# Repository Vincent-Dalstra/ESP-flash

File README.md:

# ESP-flash
A USB to UART Serial interface implementing a CH340C.

Designed primarily to program board with embedded ESP32 modules. USB-micro and USB-c for minimum I-have-the-wrong-cable

For compatibility with other programmers, it follow the the ESPFlash 1x6 Header convention. https://github.com/SuperHouse/ESPFlash
Big thanks to them for developing it and putting it out there.

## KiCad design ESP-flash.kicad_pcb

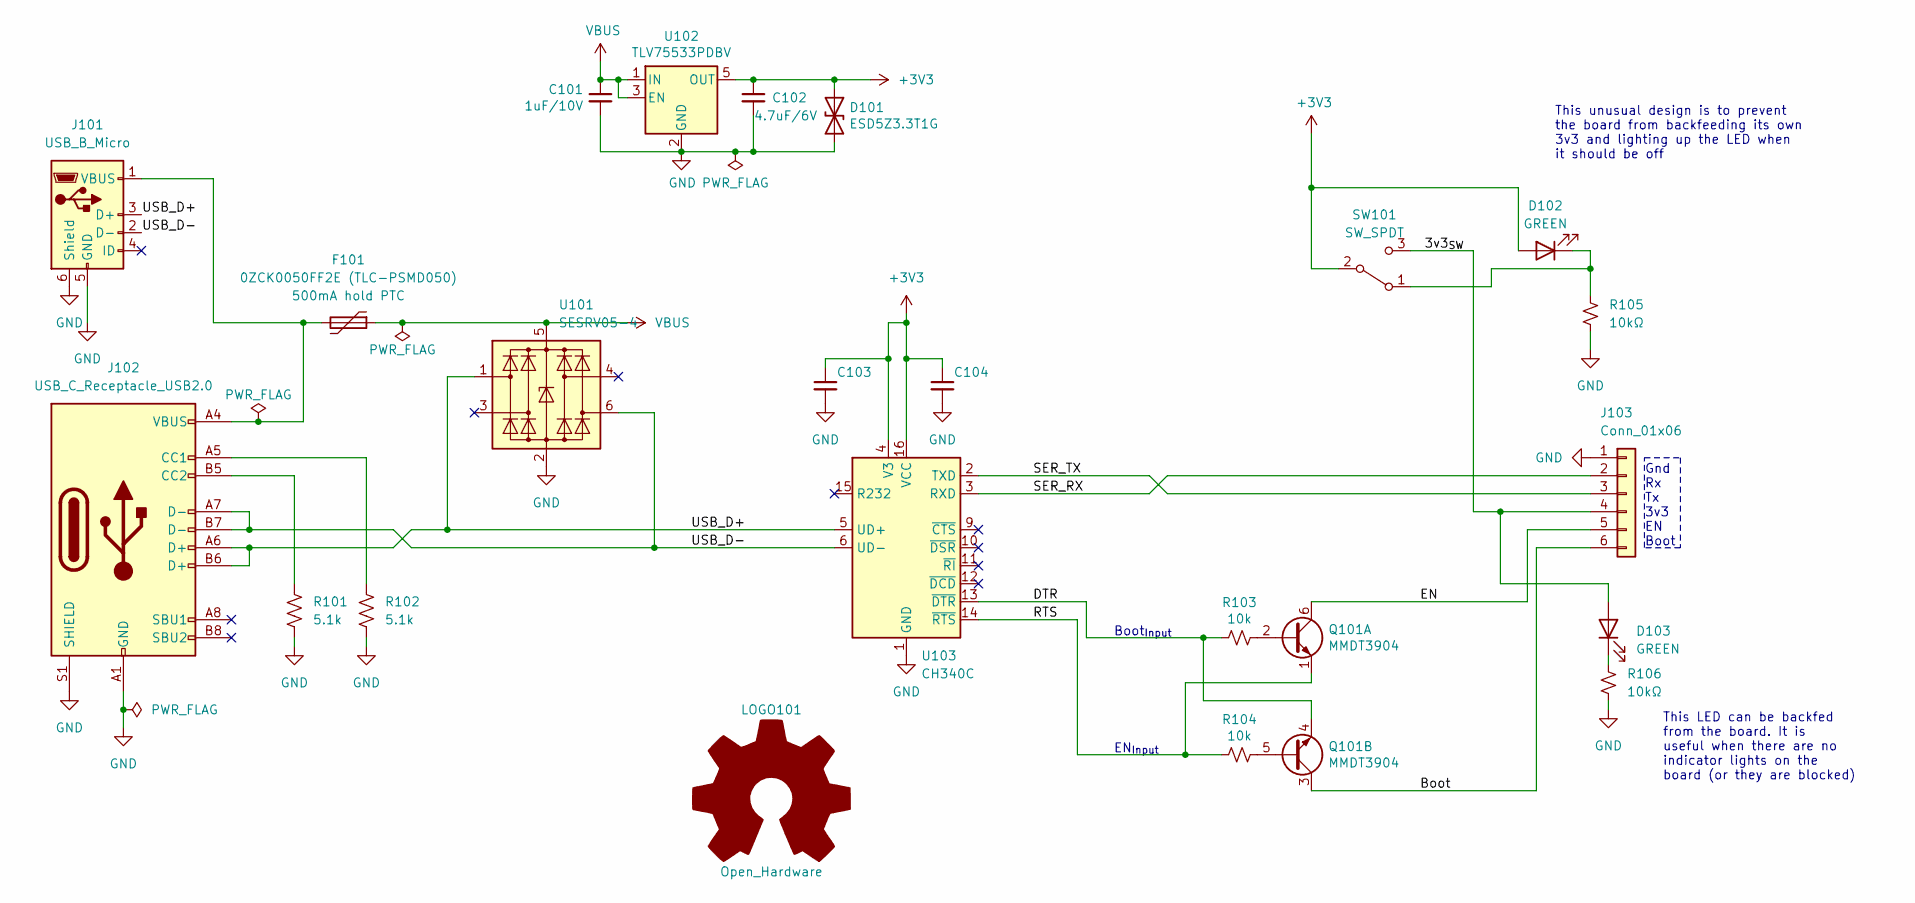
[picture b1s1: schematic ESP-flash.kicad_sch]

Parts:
C101: 1uF/10V; C_0805_2012Metric; LCSC C28323
C102: 4.7uF/6V; C_0805_2012Metric; LCSC C1779
C103: C14663; C_0603_1608Metric; LCSC C14663
C104: 10nF; C_0603_1608Metric; LCSC C14663
D101: ESD5Z3.3T1G; D_SOD-523; LCSC C61148
D102, D103: GREEN; LED_0603_1608Metric; LCSC C779453
F101: 0ZCK0050FF2E (TLC-PSMD050); Fuse_0805_2012Metric_Pad1.15x1.40mm_HandSolder; LCSC C516070
J101: USB_B_Micro; USB_Micro-B_Amphenol_10118194_Horizontal; LCSC C132563
J102: USB_C_Receptacle_USB2.0; USB_C_Receptacle_HRO_TYPE-C-31-M-12; LCSC C165948
J103: Conn_01x06; PinHeader_1x06_P2.54mm_Horizontal; LCSC C40877
LOGO101: Open_Hardware; OSHW-Logo2_7.3x6mm_SilkScreen
Q101: MMDT3904; SOT-363_SC-70-6; LCSC C83572
R101, R102: 5.1k; R_0603_1608Metric; LCSC C23186
R103, R104: 10k; R_0805_2012Metric; LCSC C17414
R105, R106: 10kΩ; R_0603_1608Metric; LCSC C25804
SW101: SW_SPDT; SW_SPDT_PCM12; LCSC C221841
U101: SESRV05-4; SOT-23-6; LCSC C294963
U102: TLV75533PDBV; SOT-23-5; LCSC C2937042
U103: CH340C; SOIC-16_3.9x9.9mm_P1.27mm; LCSC C84681

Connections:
+3V3: C102.1, C103.1, C104.1, D101.1 (A1), D102.2 (A), SW101.2 (B), U102.5 (OUT), U103.4 (V3), U103.16 (VCC)
/3v3_{SW}: D103.2 (A), J103.4, SW101.3 (C)
/Boot: J103.6, Q101.3 (C2)
/DTR: Q101.4 (E2), R103.2, U103.13 (~DTR)
/EN: J103.5, Q101.6 (C1)
/RTS: Q101.1 (E1), R104.2, U103.14 (~RTS)
/SER_RX: J103.2, U103.3 (RXD)
/SER_TX: J103.3, U103.2 (TXD)
/USB_D+: J101.3 (D+), J102.A6 (D+), J102.B6 (D+), U101.1 (I/O1), U103.5 (UD+)
/USB_D-: J101.2 (D-), J102.A7 (D-), J102.B7 (D-), U101.6 (I/O4), U103.6 (UD-)
GND: C101.2, C102.2, C103.2, C104.2, D101.2 (A2), J101.5 (GND), J101.6 (Shield), J102.A1 (GND), J102.A12 (GND), J102.B1 (GND), J102.B12 (GND), J102.S1 (SHIELD), J103.1, R101.1, R102.1, R105.2, R106.2, U101.2 (GND), U102.2 (GND), U103.1 (GND)
unnamed: D102.1 (K), R105.1, SW101.1 (A)
unnamed: D103.1 (K), R106.1
unnamed: F101.2, J101.1 (VBUS), J102.A4 (VBUS), J102.A9 (VBUS), J102.B4 (VBUS), J102.B9 (VBUS)
unnamed: J102.A5 (CC1), R102.2
unnamed: J102.B5 (CC2), R101.2
unnamed: Q101.2 (B1), R103.1
unnamed: Q101.5 (B2), R104.1
VBUS: C101.1, F101.1, U101.5 (VBUS), U102.1 (IN), U102.3 (EN)

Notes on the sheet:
Gnd Rx Tx 3v3 EN Boot
Boot_{Input}
EN_{Input}
This unusual design is to prevent the board from backfeeding its own 3v3 and lighting up the LED when it should be off
This LED can be backfed from the board. It is useful when there are no indicator lights on the board (or they are blocked)

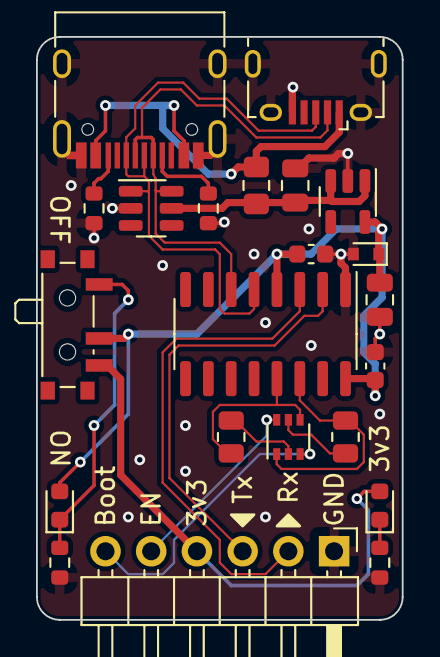
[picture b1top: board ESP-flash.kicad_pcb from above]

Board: 2 copper layers, 20.3 x 32.4 mm, 23 parts (1 on the bottom side), 19 nets.

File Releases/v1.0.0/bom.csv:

Comment,Designator,Footprint,LCSC
1uF/10V,C101,Capacitor_SMD:C_0805_2012Metric,C28323
4.7uF/6V,C102,Capacitor_SMD:C_0805_2012Metric,C1779
100nF,"C103,C104",Capacitor_SMD:C_0603_1608Metric,C14663
ESD5Z3.3T1G,D101,Diode_SMD:D_SOD-523,C61148
GREEN,D102,LED_SMD:LED_0603_1608Metric,C72043
0ZCK0050FF2E (TLC-PSMD050),F101,Fuse:Fuse_0805_2012Metric_Pad1.15x1.40mm_HandSolder,C261942
USB_B_Micro,J101,Connector_USB_custom:USB_Micro-B_Amphenol_10118194_Horizontal,C132563
USB_C_Receptacle_USB2.0,J102,Connector_USB:USB_C_Receptacle_HRO_TYPE-C-31-M-12,C165948
MMDT3904,Q101,Package_TO_SOT_SMD:SOT-363_SC-70-6,C83572
5.1k,"R101,R102",Resistor_SMD:R_0603_1608Metric,C23186
10k,"R103,R104",Resistor_SMD:R_0805_2012Metric,C17414
10kΩ,R105,Resistor_SMD:R_0603_1608Metric,C25804
SW_SPDT,SW101,Button_Switch_SMD:SW_SPDT_PCM12,C109335
ESD PROTECTION,U101,Package_TO_SOT_SMD:SOT-23-6,C294963
TLV75533PDBV,U102,Package_TO_SOT_SMD:SOT-23-5,C404027
CH340C,U103,Package_SO:SOIC-16_3.9x9.9mm_P1.27mm,C84681

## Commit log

2022-12-09 Created from template, schematic complete
2022-12-20 PCB complete
2022-12-23 Sent to board fab v1.0.0
2023-01-03 Sent to board fab v1.0.1, replaces previous
    Changes:
    - USB diodes out of stock; different manufacturer had their stock.
    - SPDT switch out of stock, replaced with a different switch that
    thankfully also had a footprint in KiCAD
    - Made the board slightly wider to accomodate the switch.
2023-02-15 Bugfix: PWR LED backfed from board
    Power LED would light up when board was using its own 3v3 Power, even
    though the switch was in the off position.
    Found a clever solution to fix this, by changing two short traces.
2023-05-19 Added Silskcreen gnd-pin indicator
    To match up with the arrows on PCB's that use this programmer.
2023-06-30 Changed from right-angled to straight shape
    For a lot of boards, the sideways design means the cable tends to get in
    the way of things, especially cases. A straight-through format that can
    be plugged in vertically would do much better.
2023-07-01 Add 2nd indicator LED
    - The first one is linked to the switch, and indicates when the switch
    is closed, linking the 3v3 nets together.
    - The second one is linked directly to the 3v3 pin on the programmer. It
    will also turn on when the target board has its own power source.
2023-07-13 Convert to 7.0 format, fix DRC errors
    Opened and saved with KiCAD 7.0
    Fix a few unconnected components. Adjusted DRC violation severities to
    ignore silkscreen over board edge (because they're usually on purpose
    and don't help track down errors).
2023-09-26 squash! Sent to baord fab [1.1.0]
    Made the ESD protection IC a library symbol.
2024-03-08 Improve .gitignore
2025-06-26 Bump version number, fix name, update makefile and .gitignore
2025-06-27 Substitute out-of-stock components
    Unsurprising considering how long ago this was last ordered, some of the
    components were no longer stocked.
    - Green LED (already had a replacement, in other PCB designs)
    - Polyfuse (easily found another one on JLCPCB)
    - The SPDT switch (couldn't find an exact replacement, and ended up
    using another type with a already-available footprint).
2025-07-15 Move USB section into subsheet
2025-07-15 Debugging kicanvas: move subsheet into root folder
